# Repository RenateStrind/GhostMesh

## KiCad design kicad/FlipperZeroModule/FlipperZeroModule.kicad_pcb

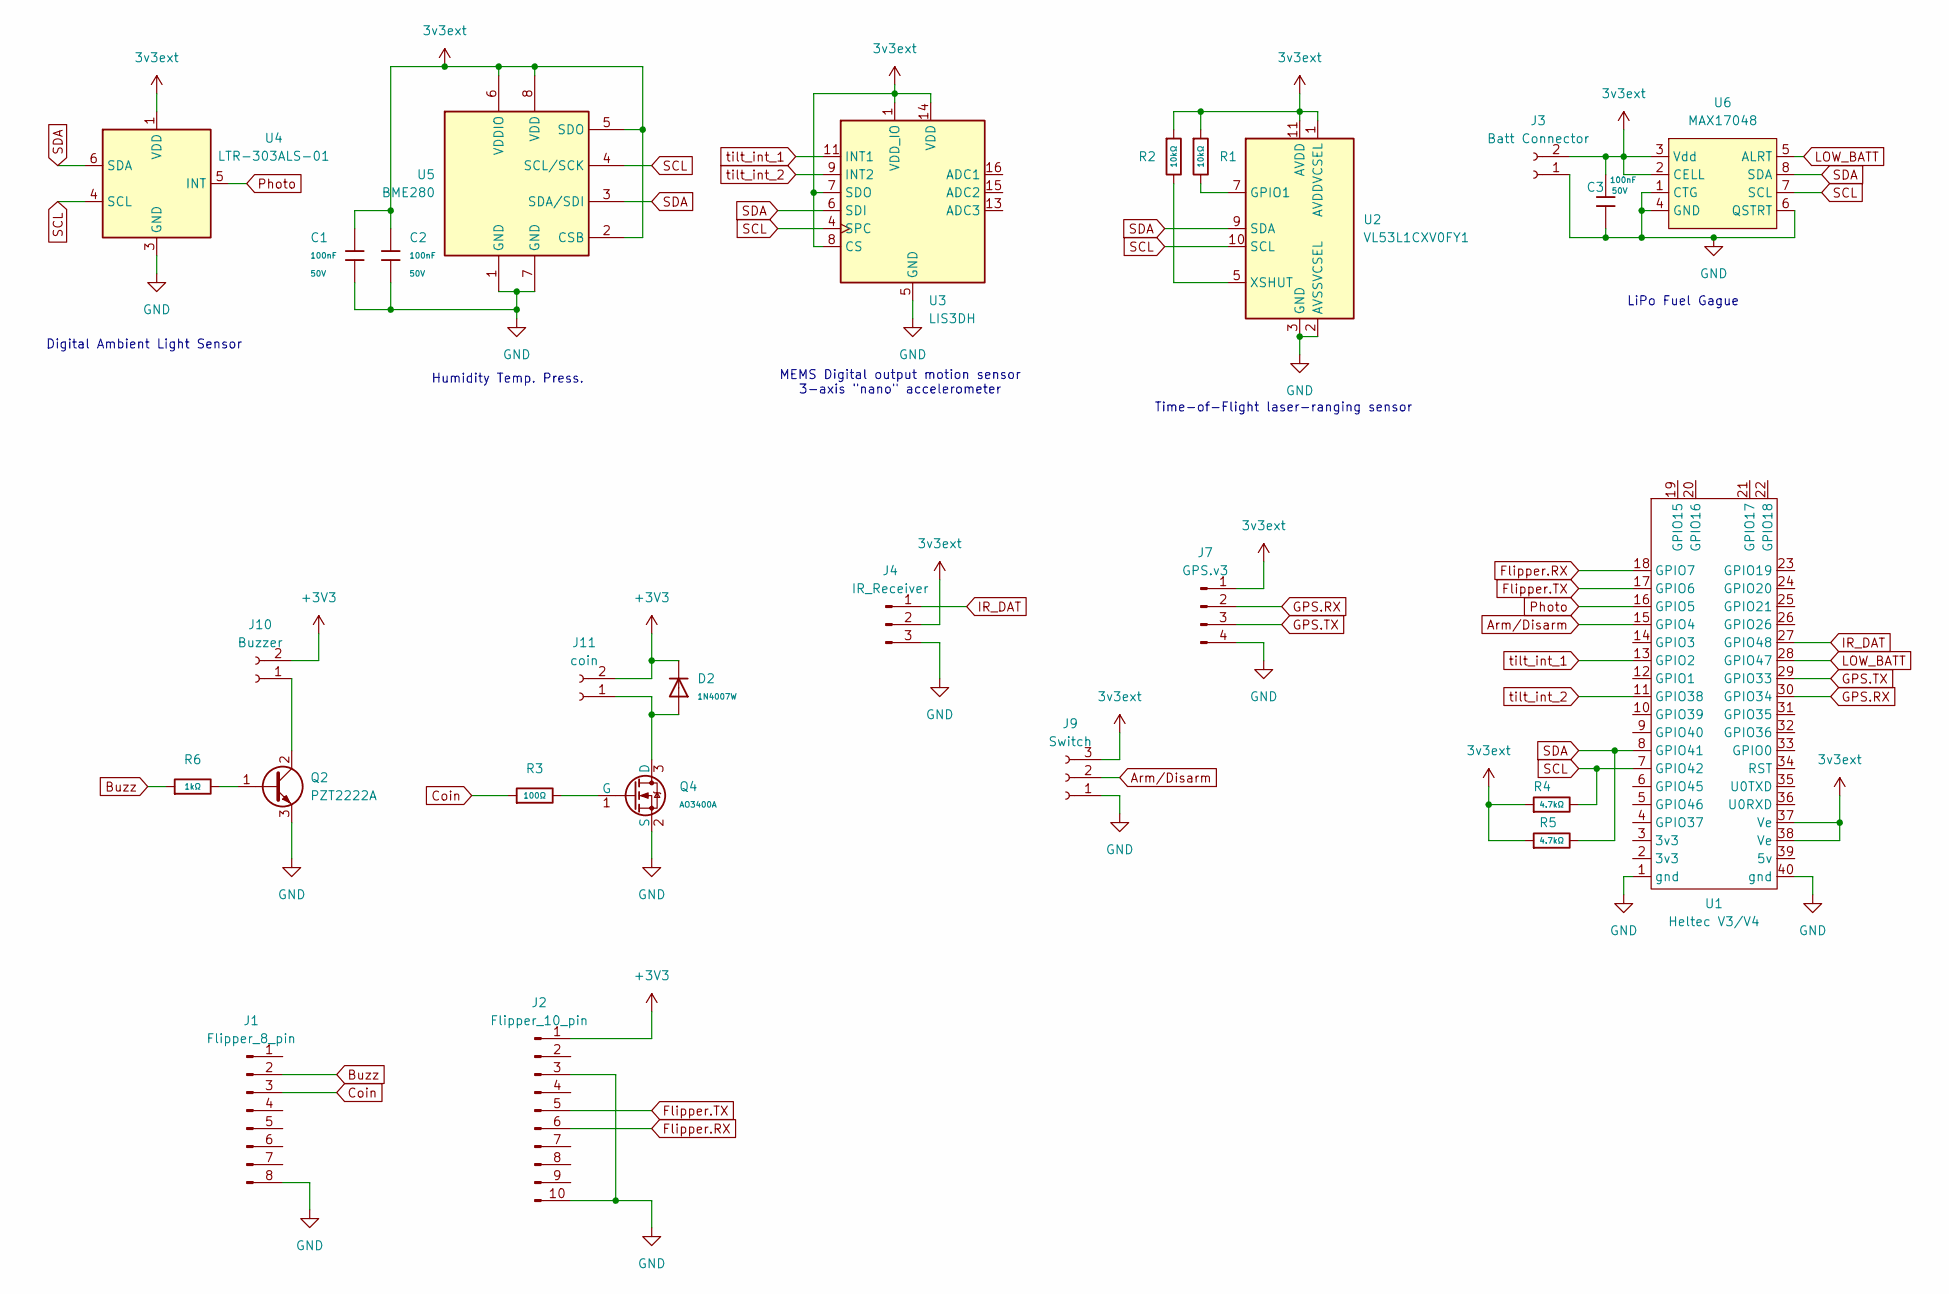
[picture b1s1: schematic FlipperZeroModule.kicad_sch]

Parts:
C1, C2, C3: 100nF; C_0603; Voltage Rated 50V; Tolerance ±10%; Part CC0603KRX7R9BB104; LCSC C14663
D2: 1N4007W; D_SOD-123FL; Part 1N4007W; LCSC C18199088
J1: Flipper_8_pin; PinHeader_1x08_P2.54mm_Vertical
J2: Flipper_10_pin; PinHeader_1x10_P2.54mm_Vertical
J3: Batt Connector; JST_PH_S2B-PH-K_1x02_P2.00mm_Horizontal
J4: IR_Receiver; PinHeader_1x03_P2.54mm_Vertical
J7: GPS.v3; PinHeader_1x04_P2.54mm_Vertical
J9: Switch; PinHeader_1x03_P2.54mm_Vertical
J10: Buzzer; PinHeader_1x02_P2.54mm_Vertical
J11: coin; PinHeader_1x02_P2.54mm_Vertical
Q2: PZT2222A; SOT-223-3_TabPin2
Q4: AO3400A; Q_SOT-23; Part AO3400A; LCSC C20917
R1, R2: 10kΩ; R_0603; Overload Voltage (Max) 75V; Tolerance ±1%; Part 0603WAF1002T5E; LCSC C25804
R3: 100Ω; R_0603; Overload Voltage (Max) 75V; Tolerance ±1%; Part 0603WAF1000T5E; LCSC C22775
R4, R5: 4.7kΩ; R_0603; Overload Voltage (Max) 75V; Tolerance ±1%; Part 0603WAF4701T5E; LCSC C23162
R6: 1kΩ; R_0603; Overload Voltage (Max) 75V; Tolerance ±1%; Part 0603WAF1001T5E; LCSC C21190
U1: Heltec V3/V4; heltech v4
U2: VL53L1CXV0FY1; ST_VL53L1x
U3: LIS3DH; LGA-16_3x3mm_P0.5mm_LayoutBorder3x5y
U4: LTR-303ALS-01; Lite-On_LTR-303ALS-01; LCSC C364577
U5: BME280; Bosch_LGA-8_2.5x2.5mm_P0.65mm_ClockwisePinNumbering; LCSC C92489
U6: MAX17048; TDFN-8-1EP_2x2mm_P0.5mm_EP0.8x1.2mm

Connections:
3v3ext: C1.1, C2.1, C3.1, J3.2, J4.2, J7.1, J9.3, R1.1, R2.1, R4.1, R5.1, U1.37 (Ve), U1.38 (Ve), U2.1 (AVDDVCSEL), U2.11 (AVDD), U3.1 (VDD_IO), U3.7 (SDO), U3.8 (CS), U3.14 (VDD), U4.1 (VDD), U5.2 (CSB), U5.5 (SDO), U5.6 (VDDIO), U5.8 (VDD), U6.2 (CELL), U6.3 (Vdd)
+3V3: D2.1, J2.1, J10.2, J11.2
Arm/Disarm: J9.2, U1.15 (GPIO4)
Buzz: J1.2, R6.1
Coin: J1.3, R3.1
Flipper.RX: J2.6, U1.18 (GPIO7)
Flipper.TX: J2.5, U1.17 (GPIO6)
GND: C1.2, C2.2, C3.2, J1.8, J2.3, J2.10, J3.1, J4.3, J7.4, J9.1, Q2.3 (E), Q4.2 (S), U1.1 (gnd), U1.40 (gnd), U2.2 (AVSSVCSEL), U2.3 (GND), U2.4 (GND), U2.6 (GND), U2.12 (GND), U3.5 (GND), U3.10 (GND), U3.12 (GND), U4.3 (GND), U5.1 (GND), U5.7 (GND), U6.1 (CTG), U6.4 (GND), U6.6 (QSTRT)
GPS.RX: J7.2, U1.30 (GPIO34)
GPS.TX: J7.3, U1.29 (GPIO33)
IR_DAT: J4.1, U1.27 (GPIO48)
LOW_BATT: U1.28 (GPIO47), U6.5 (ALRT)
unnamed: J10.1, Q2.2 (C)
unnamed: D2.2, J11.1, Q4.3 (D)
unnamed: Q2.1 (B), R6.2
unnamed: Q4.1 (G), R3.2
unnamed: R1.2, U2.7 (GPIO1)
unnamed: R2.2, U2.5 (XSHUT)
Photo: U1.16 (GPIO5), U4.5 (INT)
SCL: R4.2, U1.7 (GPIO42), U2.10 (SCL), U3.4 (SPC), U4.4 (SCL), U5.4 (SCL/SCK), U6.7 (SCL)
SDA: R5.2, U1.8 (GPIO41), U2.9 (SDA), U3.6 (SDI), U4.6 (SDA), U5.3 (SDA/SDI), U6.8 (SDA)
tilt_int_1: U1.13 (GPIO2), U3.11 (INT1)
tilt_int_2: U1.11 (GPIO38), U3.9 (INT2)

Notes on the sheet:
MEMS Digital output motion sensor 3-axis "nano" accelerometer
Humidity Temp. Press.
Digital Ambient Light Sensor
LiPo Fuel Gague
Time-of-Flight laser-ranging sensor

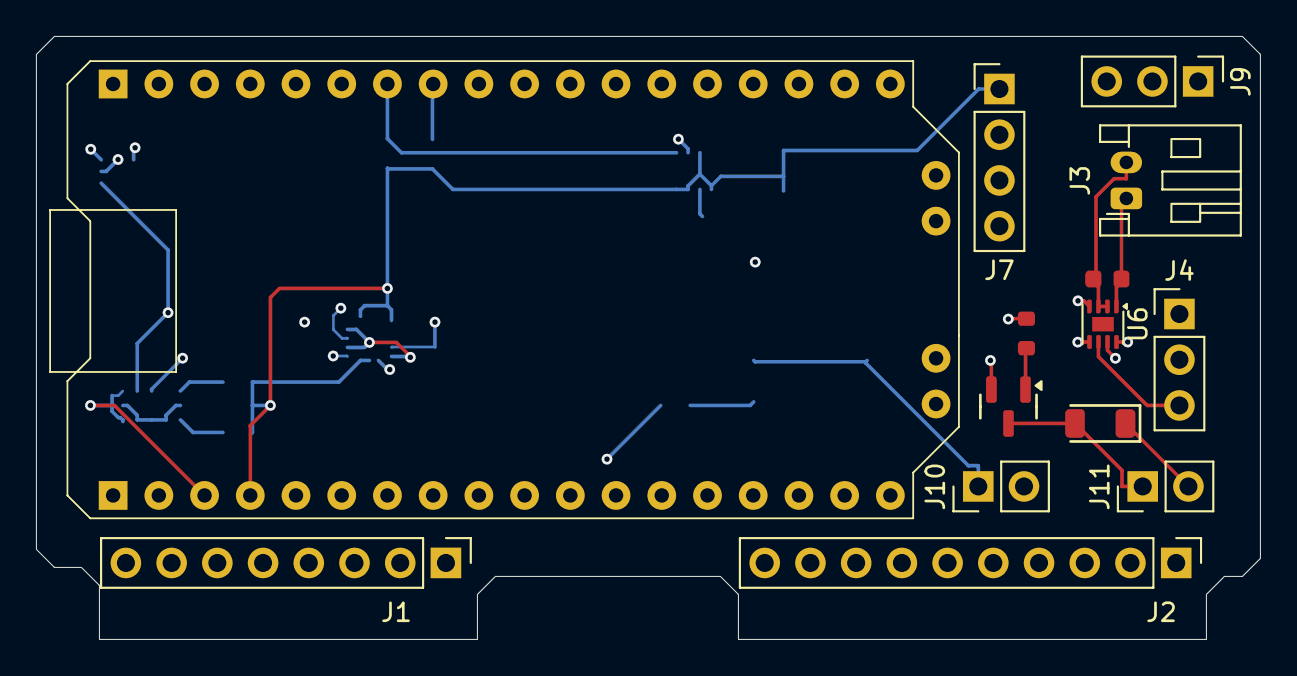
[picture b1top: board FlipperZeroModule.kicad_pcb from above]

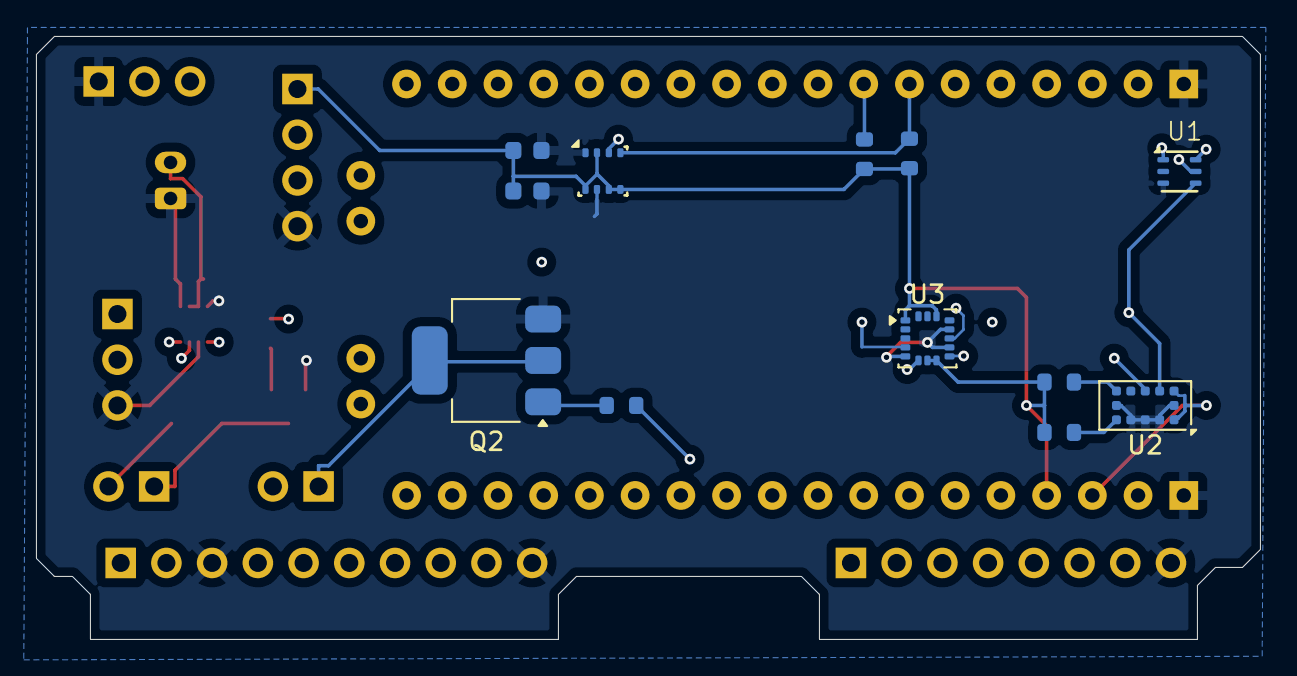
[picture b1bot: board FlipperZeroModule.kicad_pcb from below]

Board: 4 copper layers, 68.0 x 33.5 mm, 26 parts (12 on the bottom side), 23 nets.
